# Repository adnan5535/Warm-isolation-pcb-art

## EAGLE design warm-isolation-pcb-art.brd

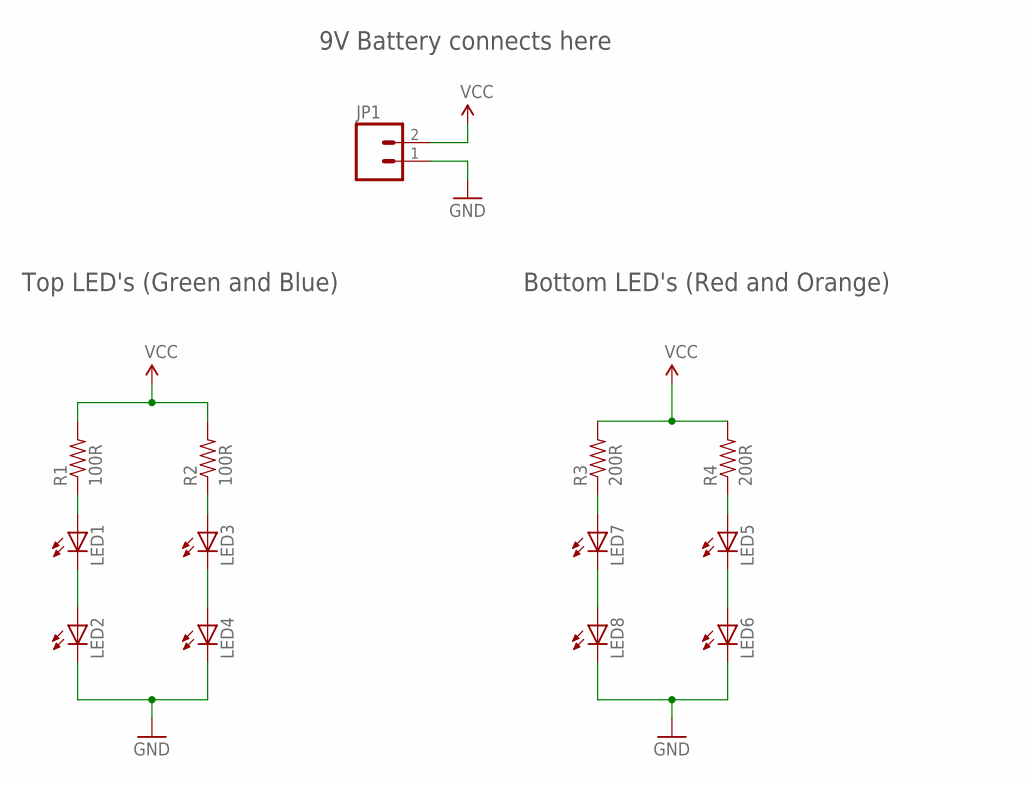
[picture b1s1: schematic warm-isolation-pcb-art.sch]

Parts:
JP1: M02LOCK; 1X02_LOCK
LED1, LED2, LED3, LED4, LED5, LED6, LED7, LED8: LEDCHIP-LED0805; CHIP-LED0805
R1, R2: 100R; 0805
R3, R4: 200R; 0805

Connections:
GND: JP1.1, LED2.C, LED4.C, LED6.C, LED8.C
unnamed: LED1.A, R1.1
unnamed: LED3.A, R2.1
unnamed: LED1.C, LED2.A
unnamed: LED3.C, LED4.A
unnamed: LED7.A, R3.1
unnamed: LED7.C, LED8.A
unnamed: LED5.C, LED6.A
unnamed: LED5.A, R4.1
VCC: JP1.2, R1.2, R2.2, R3.2, R4.2

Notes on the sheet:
Top LED's (Green and Blue)
Bottom LED's (Red and Orange)
9V Battery connects here

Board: 2 copper layers, 13 parts (4 on the bottom side), 10 nets, no tracks yet.

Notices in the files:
parts and their libraries:
SparkFun: Licensing: CC v3.0 Share-Alike You are welcome to use this library for commercial purposes.
